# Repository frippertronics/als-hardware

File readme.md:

# Annoying Little Shit hardware

This repository contains the KiCAD design files for the
Annoying Little Shit (ALS) device, which is an AVR ATTiny13-based
device which wakes up at random intervals and beeps loudly. It is
designed to be annoying.

The buzzer is rated at 80 dB @ 4 kHz, and testing has found it to
be loud enough!

The firmware for the device can be found [here](https://github.com/frippertronics/als)!

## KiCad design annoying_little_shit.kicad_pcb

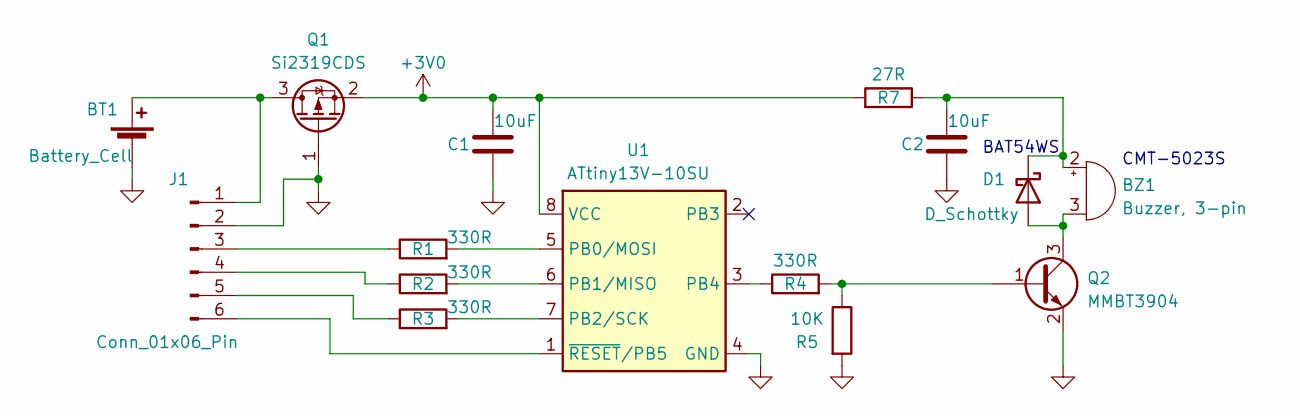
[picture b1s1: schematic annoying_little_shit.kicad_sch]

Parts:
BT1: Battery_Cell; BatteryHolder_Keystone_3002_1x2032
BZ1: Buzzer, 3-pin; MagneticBuzzer_CUI_CMT-5023S-SMT
C1, C2: 10uF; C_0603_1608Metric
D1: D_Schottky; D_SOD-323_HandSoldering
J1: Conn_01x06_Pin; PinHeader_1x06_P1.00mm_Vertical_SMD_Aligned
Q1: Si2319CDS; SOT-23
Q2: MMBT3904; SOT-23
R1, R2, R3, R4: 330R; R_0603_1608Metric
R5: 10K; R_0603_1608Metric
R7: 27R; R_0603_1608Metric
U1: ATtiny13V-10SU; SOIC-8W_5.3x5.3mm_P1.27mm

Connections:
+3V0: C1.1, Q1.2 (S), R7.2, U1.8 (VCC)
GND: BT1.2 (-), C1.2, C2.2, J1.2, Q1.1 (G), Q2.2 (E), R5.2, U1.4 (GND)
unnamed: BT1.1 (+), J1.1, Q1.3 (D)
unnamed: BZ1.2 (+), C2.1, D1.1 (K), R7.1
unnamed: BZ1.3 (-), D1.2 (A), Q2.3 (C)
unnamed: J1.3, R1.1
unnamed: J1.4, R2.1
unnamed: J1.5, R3.1
unnamed: J1.6, U1.1 (~RESET/PB5)
unnamed: Q2.1 (B), R4.2, R5.1
unnamed: R1.2, U1.5 (PB0/MOSI)
unnamed: R2.2, U1.6 (PB1/MISO)
unnamed: R3.2, U1.7 (PB2/SCK)
unnamed: R4.1, U1.3 (PB4)

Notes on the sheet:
CMT-5023S
BAT54WS

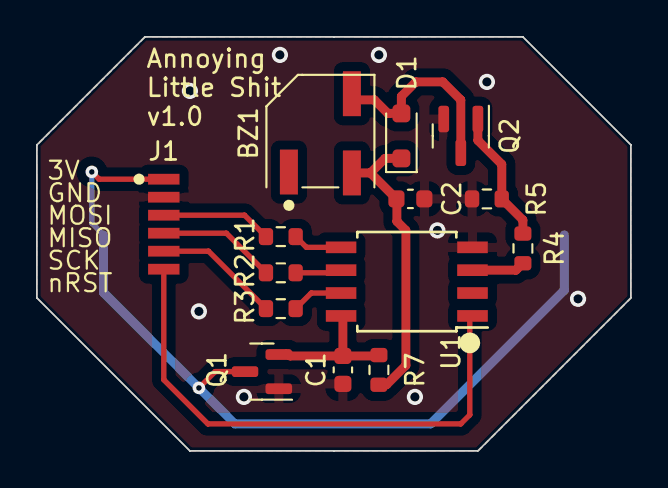
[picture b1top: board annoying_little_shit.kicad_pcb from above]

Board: 2 copper layers, 33.0 x 23.0 mm, 15 parts (1 on the bottom side), 14 nets.

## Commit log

2023-12-04 Initial commit of v0.1
2024-01-14 Version 1.0: Current limiting resistor on buzzer, larger footprint for buzzer to make it easier to solder, remove pull-up on nRST to limit current drain (there should also be an internal one on the A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
